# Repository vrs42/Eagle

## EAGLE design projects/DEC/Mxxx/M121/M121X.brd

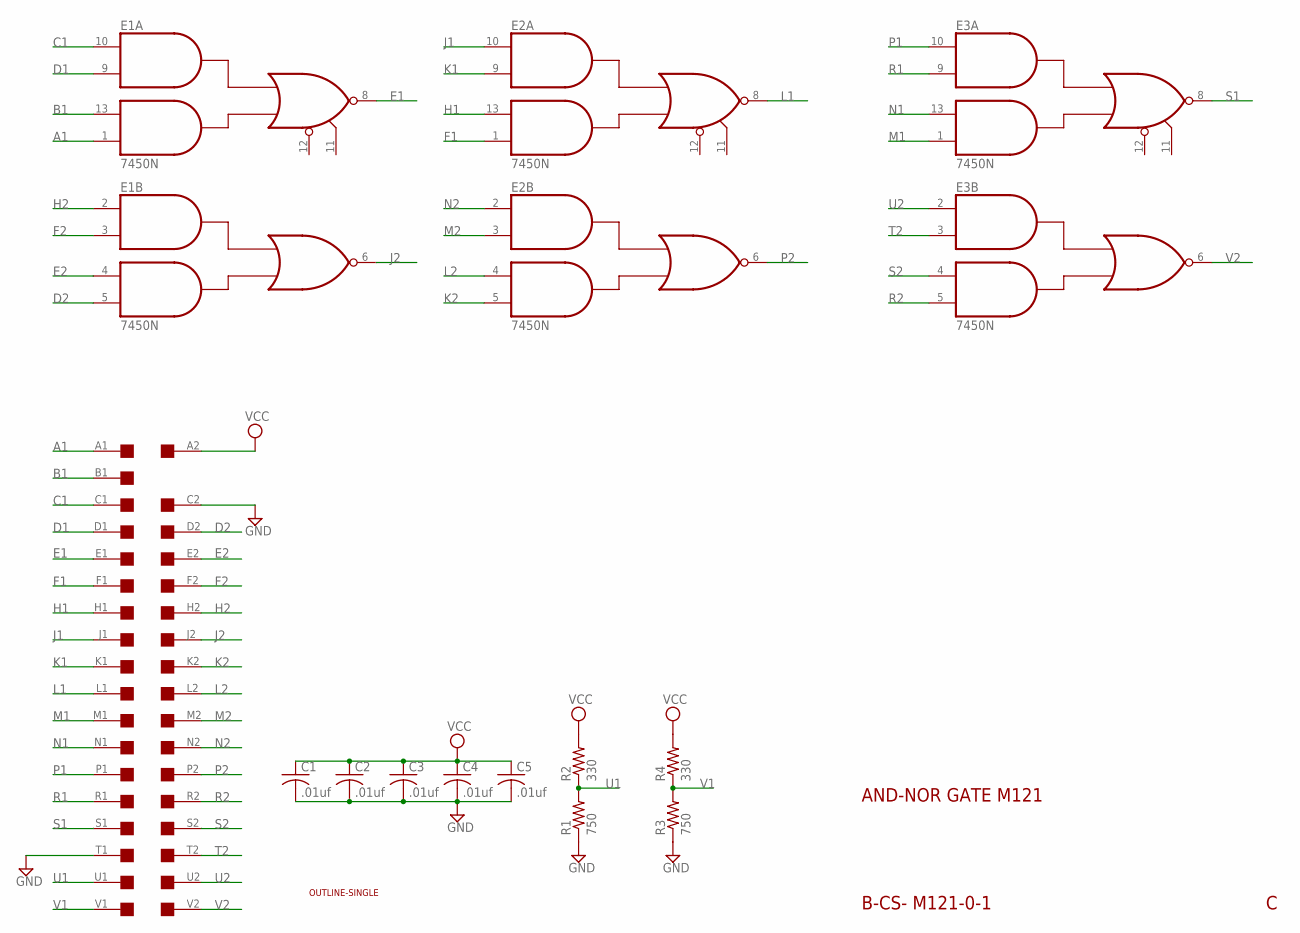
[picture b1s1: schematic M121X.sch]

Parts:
C1, C2, C3, C4, C5: .01uf; C050-025X075
E1, E2, E3: 7450N; DIL14
R1, R3: 750; 0207/10
R2, R4: 330; 0207/10
U$1: OUTLINE-SINGLE; SINGLE
U$4: SINGLE; EDGE-CON2

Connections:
A1: E1.1 (I4), U$4.A1
B1: E1.13 (I3), U$4.B1
C1: E1.10 (I1), U$4.C1
D1: E1.9 (I2), U$4.D1
D2: E1.5 (I4), U$4.D2
E1: E1.8 (O), U$4.E1
E2: E1.4 (I3), U$4.E2
F1: E2.1 (I4), U$4.F1
F2: E1.3 (I2), U$4.F2
GND: C1.2, C2.2, C3.2, C4.2, C5.2, E1.7 (GND), E2.7 (GND), E3.7 (GND), R1.1, R3.1, U$4.C2, U$4.T1
H1: E2.13 (I3), U$4.H1
H2: E1.2 (I1), U$4.H2
J1: E2.10 (I1), U$4.J1
J2: E1.6 (O), U$4.J2
K1: E2.9 (I2), U$4.K1
K2: E2.5 (I4), U$4.K2
L1: E2.8 (O), U$4.L1
L2: E2.4 (I3), U$4.L2
M1: E3.1 (I4), U$4.M1
M2: E2.3 (I2), U$4.M2
N1: E3.13 (I3), U$4.N1
N2: E2.2 (I1), U$4.N2
P1: E3.10 (I1), U$4.P1
P2: E2.6 (O), U$4.P2
R1: E3.9 (I2), U$4.R1
R2: E3.5 (I4), U$4.R2
S1: E3.8 (O), U$4.S1
S2: E3.4 (I3), U$4.S2
T2: E3.3 (I2), U$4.T2
U1: R1.2, R2.1, U$4.U1
U2: E3.2 (I1), U$4.U2
V1: R3.2, R4.1, U$4.V1
V2: E3.6 (O), U$4.V2
VCC: C1.1, C2.1, C3.1, C4.1, C5.1, E1.14 (VCC), E2.14 (VCC), E3.14 (VCC), R2.2, R4.2, U$4.A2

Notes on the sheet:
AND-NOR GATE M121
B-CS- M121-0-1

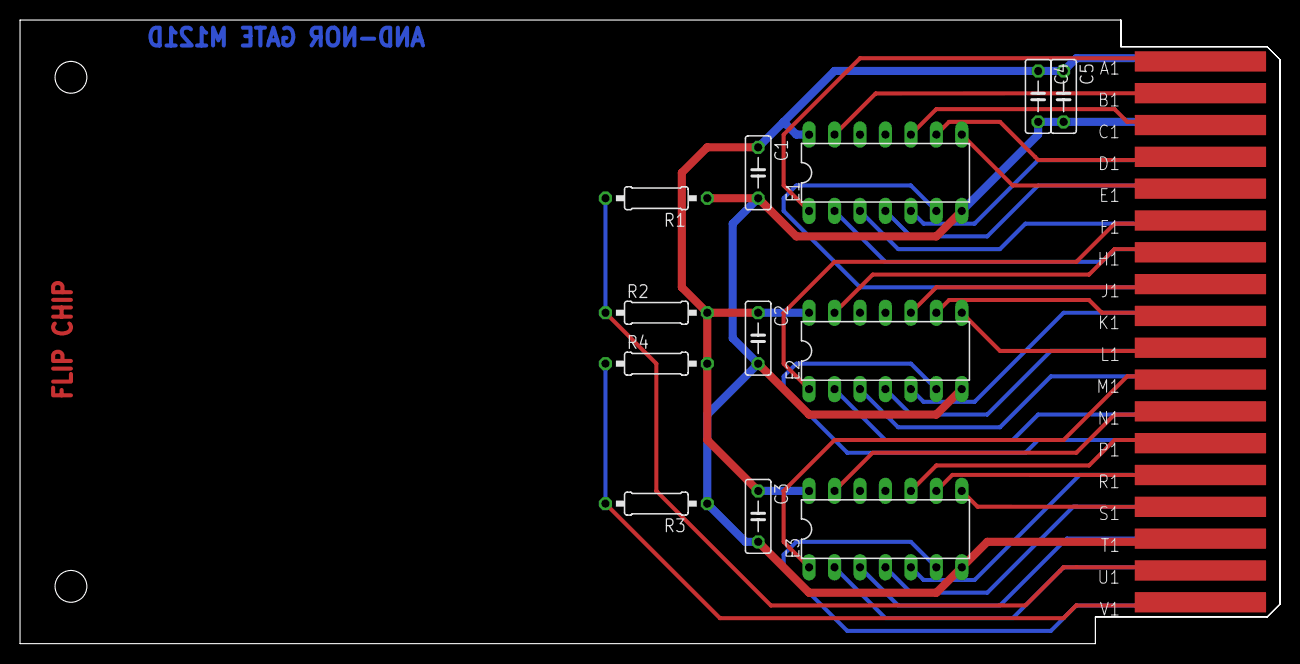
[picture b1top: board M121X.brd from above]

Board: 2 copper layers, 125.7 x 62.2 mm, 14 parts (0 on the bottom side), 34 nets.

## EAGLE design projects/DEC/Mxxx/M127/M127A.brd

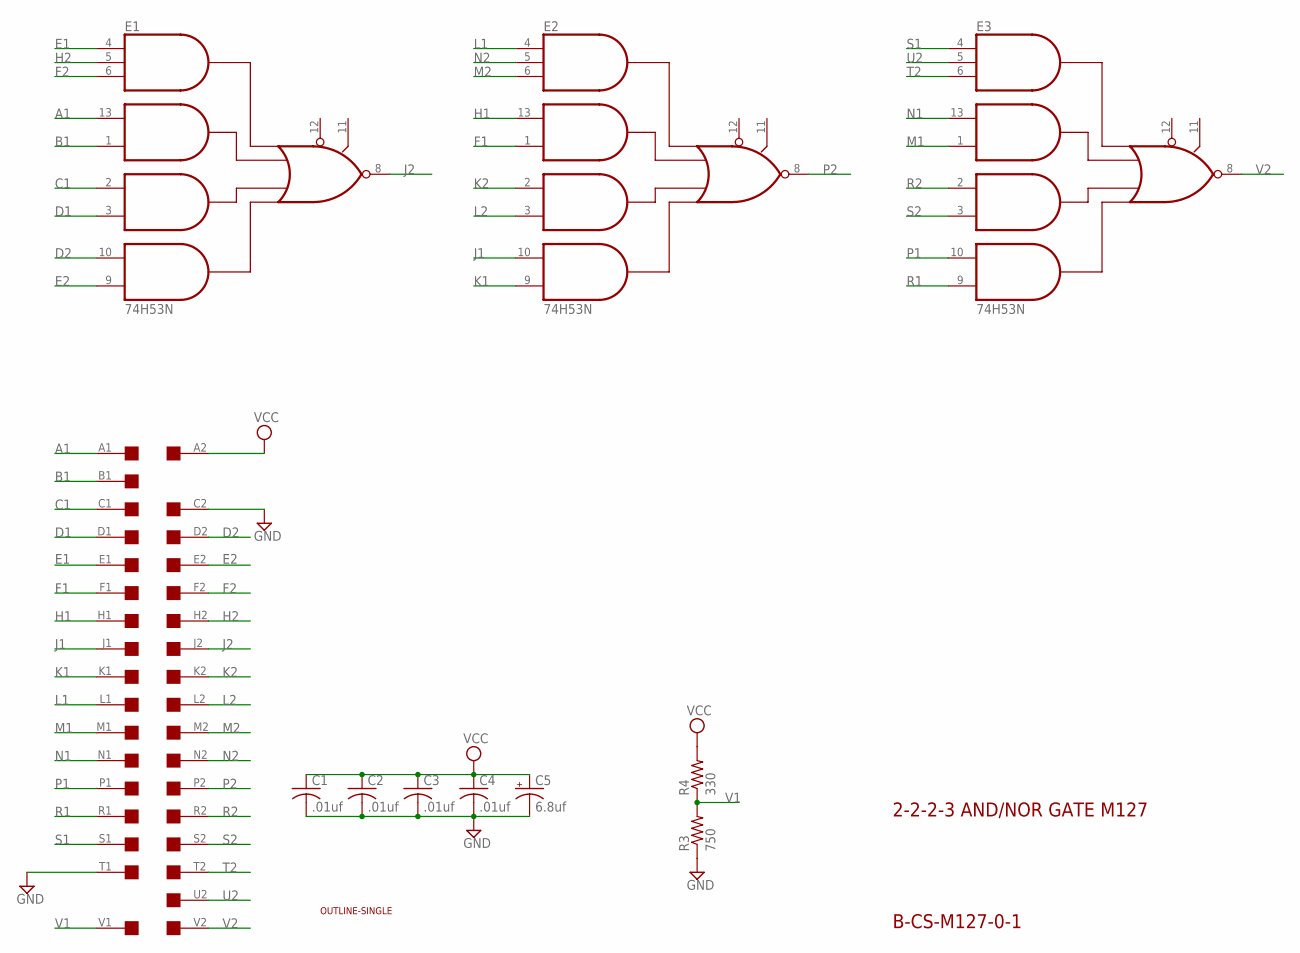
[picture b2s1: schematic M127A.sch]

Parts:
C1, C2, C3, C4: .01uf; C050-025X075
C5: 6.8uf; E15-5
E1, E2, E3: 74H53N; DIL14
R3: 750; 0207/10
R4: 330; 0207/10
U$1: OUTLINE-SINGLE; SINGLE
U$4: SINGLE; EDGE-CON2

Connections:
A1: E1.13 (I3), U$4.A1
B1: E1.1 (I4), U$4.B1
C1: E1.2 (I5), U$4.C1
D1: E1.3 (I6), U$4.D1
D2: E1.10 (I7), U$4.D2
E1: E1.4 (I1), U$4.E1
E2: E1.9 (I8), U$4.E2
F1: E2.1 (I4), U$4.F1
F2: E1.6 (I2), U$4.F2
GND: C1.2, C2.2, C3.2, C4.2, C5.-, E1.7 (GND), E2.7 (GND), E3.7 (GND), R3.1, U$4.C2, U$4.T1
H1: E2.13 (I3), U$4.H1
H2: E1.5 (I11), U$4.H2
J1: E2.10 (I7), U$4.J1
J2: E1.8 (O), U$4.J2
K1: E2.9 (I8), U$4.K1
K2: E2.2 (I5), U$4.K2
L1: E2.4 (I1), U$4.L1
L2: E2.3 (I6), U$4.L2
M1: E3.1 (I4), U$4.M1
M2: E2.6 (I2), U$4.M2
N1: E3.13 (I3), U$4.N1
N2: E2.5 (I11), U$4.N2
P1: E3.10 (I7), U$4.P1
P2: E2.8 (O), U$4.P2
R1: E3.9 (I8), U$4.R1
R2: E3.2 (I5), U$4.R2
S1: E3.4 (I1), U$4.S1
S2: E3.3 (I6), U$4.S2
T2: E3.6 (I2), U$4.T2
U2: E3.5 (I11), U$4.U2
V1: R3.2, R4.1, U$4.V1
V2: E3.8 (O), U$4.V2
VCC: C1.1, C2.1, C3.1, C4.1, C5.+, E1.14 (VCC), E2.14 (VCC), E3.14 (VCC), R4.2, U$4.A2

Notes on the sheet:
2-2-2-3 AND/NOR GATE M127
B-CS-M127-0-1

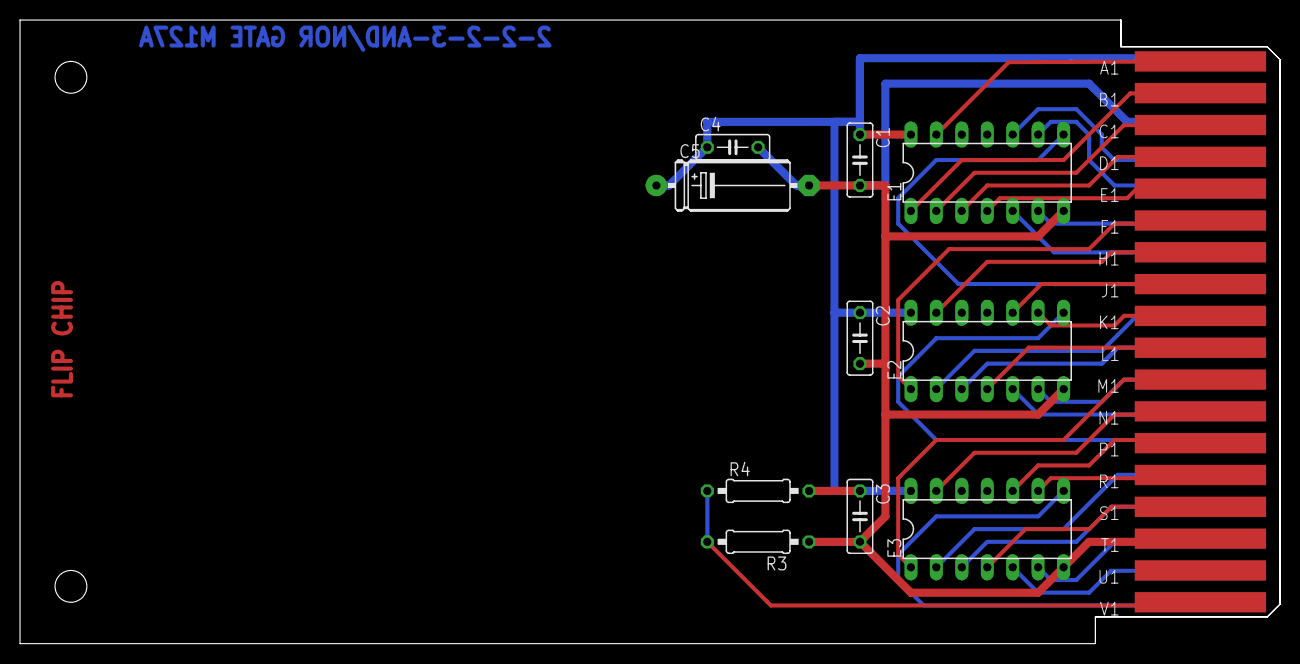
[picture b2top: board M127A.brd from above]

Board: 2 copper layers, 125.7 x 62.2 mm, 12 parts (0 on the bottom side), 33 nets.

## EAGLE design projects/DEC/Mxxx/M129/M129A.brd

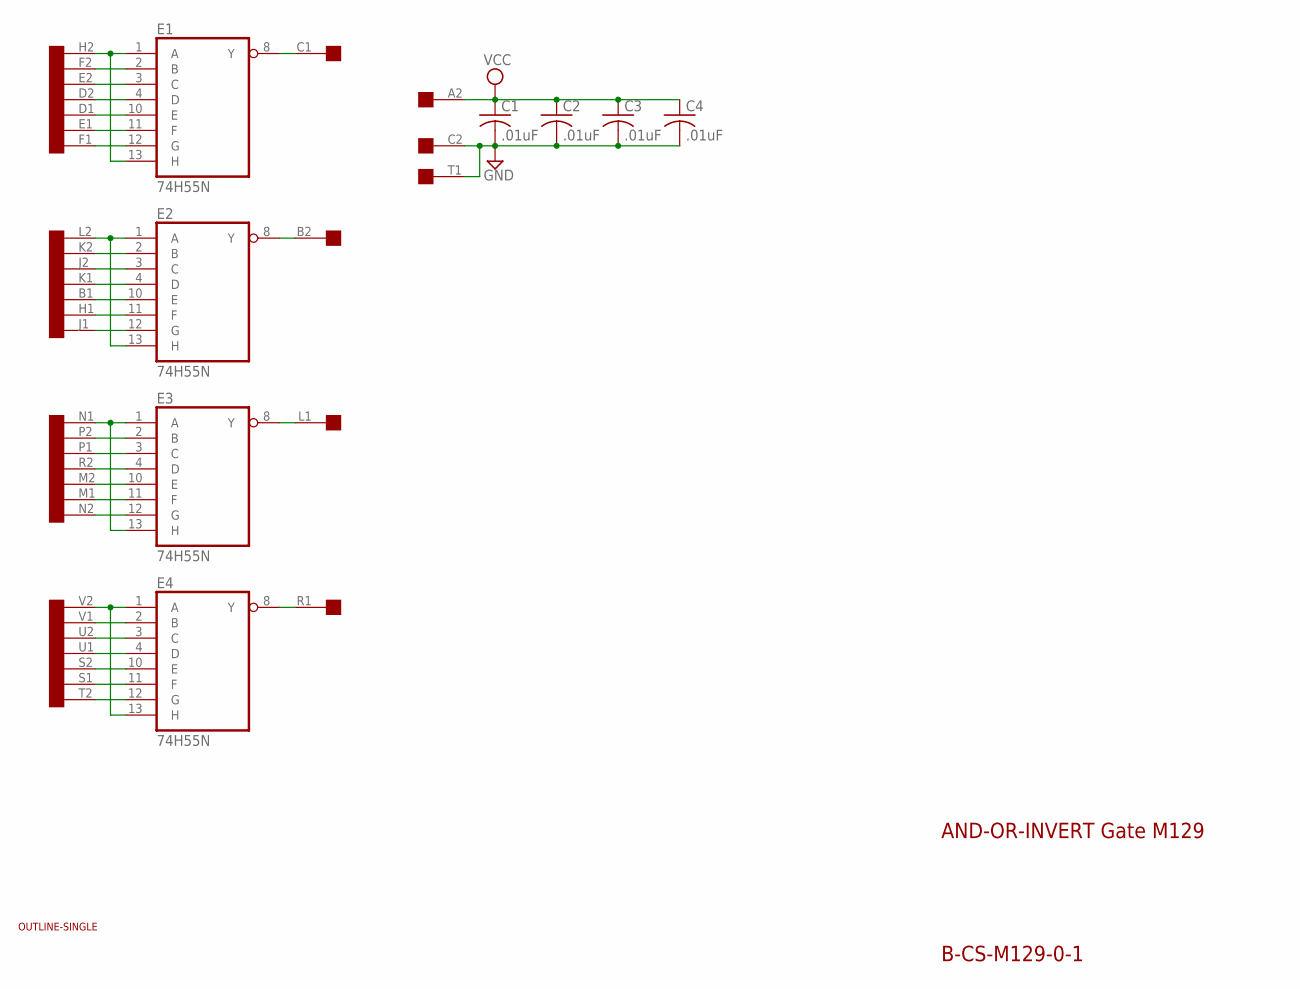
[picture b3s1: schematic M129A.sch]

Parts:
C1, C2, C3, C4: .01uF; C050-025X075
E1, E2, E3, E4: 74H55N; DIL14
U$1: SINGLE; EDGE-CON2
U$2: OUTLINE-SINGLE; SINGLE

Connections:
B1: E2.10 (E), U$1.B1
B2: E2.8 (Y), U$1.B2
C1: E1.8 (Y), U$1.C1
D1: E1.10 (E), U$1.D1
D2: E1.4 (D), U$1.D2
E1: E1.11 (F), U$1.E1
E2: E1.3 (C), U$1.E2
F1: E1.12 (G), U$1.F1
F2: E1.2 (B), U$1.F2
GND: C1.2, C2.2, C3.2, C4.2, E1.7 (GND), E2.7 (GND), E3.7 (GND), E4.7 (GND), U$1.C2, U$1.T1
H1: E2.11 (F), U$1.H1
H2: E1.1 (A), E1.13 (H), U$1.H2
J1: E2.12 (G), U$1.J1
J2: E2.3 (C), U$1.J2
K1: E2.4 (D), U$1.K1
K2: E2.2 (B), U$1.K2
L1: E3.8 (Y), U$1.L1
L2: E2.1 (A), E2.13 (H), U$1.L2
unnamed: E4.10 (E), U$1.S2
unnamed: E3.1 (A), E3.13 (H), U$1.N1
unnamed: E3.2 (B), U$1.P2
unnamed: E3.3 (C), U$1.P1
unnamed: E3.4 (D), U$1.R2
unnamed: E3.11 (F), U$1.M1
unnamed: E3.10 (E), U$1.M2
unnamed: E3.12 (G), U$1.N2
unnamed: E4.1 (A), E4.13 (H), U$1.V2
unnamed: E4.2 (B), U$1.V1
unnamed: E4.3 (C), U$1.U2
unnamed: E4.4 (D), U$1.U1
unnamed: E4.11 (F), U$1.S1
unnamed: E4.12 (G), U$1.T2
R1: E4.8 (Y), U$1.R1
VCC: C1.1, C2.1, C3.1, C4.1, E1.14 (VCC), E2.14 (VCC), E3.14 (VCC), E4.14 (VCC), U$1.A2

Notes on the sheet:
AND-OR-INVERT Gate M129
B-CS-M129-0-1

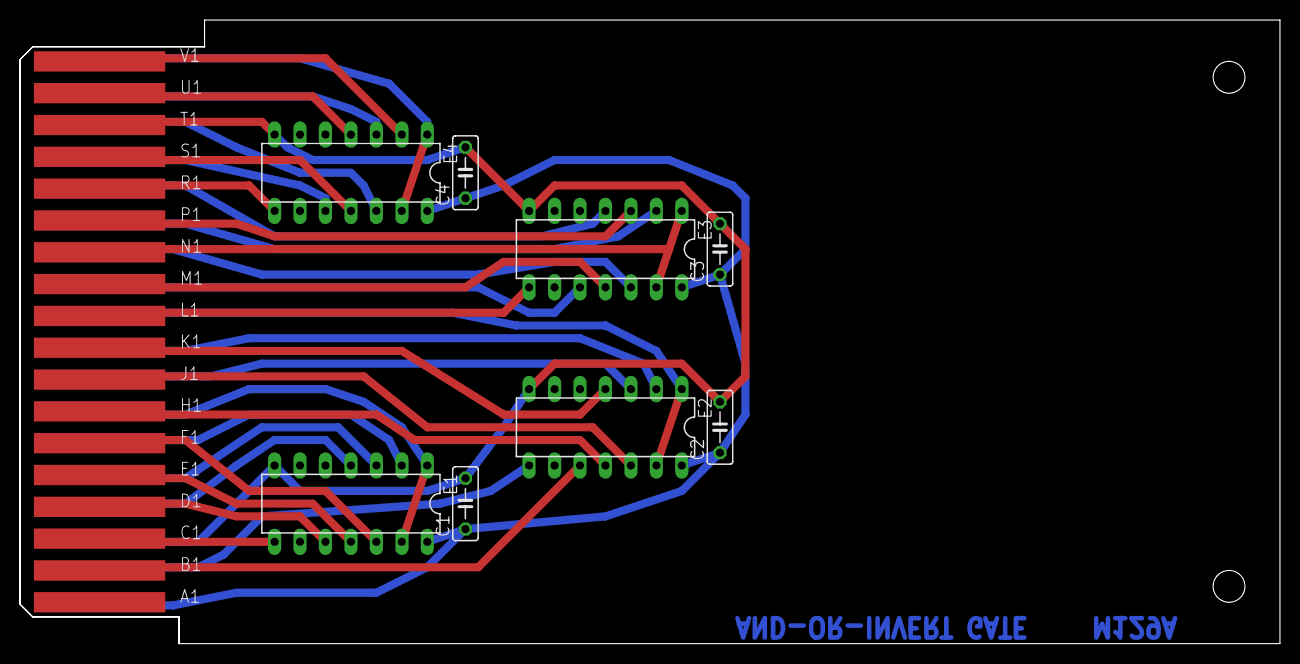
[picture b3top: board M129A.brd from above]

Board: 2 copper layers, 125.7 x 62.2 mm, 10 parts (0 on the bottom side), 34 nets.

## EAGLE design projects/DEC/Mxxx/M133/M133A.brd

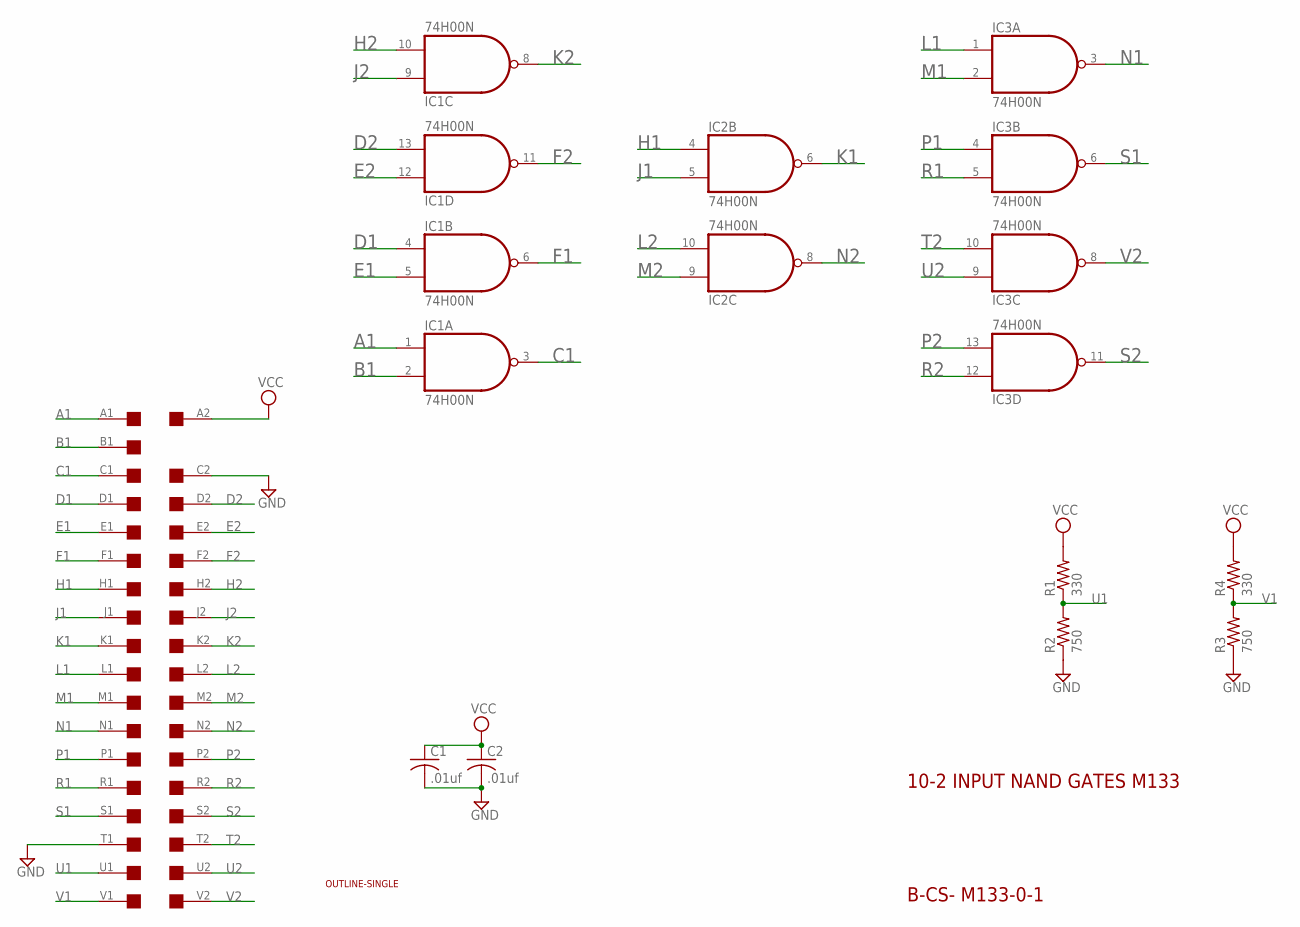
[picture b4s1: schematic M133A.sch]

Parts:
C1, C2: .01uf; C050-025X075
IC1, IC2, IC3: 74H00N; DIL14
R1, R4: 330; 0207/10
R2, R3: 750; 0207/10
U$1: OUTLINE-SINGLE; SINGLE
U$4: SINGLE; EDGE-CON2

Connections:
A1: IC1.1 (I0), U$4.A1
B1: IC1.2 (I1), U$4.B1
C1: IC1.3 (O), U$4.C1
D1: IC1.4 (I0), U$4.D1
D2: IC1.13 (I1), U$4.D2
E1: IC1.5 (I1), U$4.E1
E2: IC1.12 (I0), U$4.E2
F1: IC1.6 (O), U$4.F1
F2: IC1.11 (O), U$4.F2
GND: C1.2, C2.2, IC1.7 (GND), IC2.7 (GND), IC3.7 (GND), R2.1, R3.1, U$4.C2, U$4.T1
H1: IC2.4 (I0), U$4.H1
H2: IC1.10 (I1), U$4.H2
J1: IC2.5 (I1), U$4.J1
J2: IC1.9 (I0), U$4.J2
K1: IC2.6 (O), U$4.K1
K2: IC1.8 (O), U$4.K2
L1: IC3.1 (I0), U$4.L1
L2: IC2.10 (I1), U$4.L2
M1: IC3.2 (I1), U$4.M1
M2: IC2.9 (I0), U$4.M2
N1: IC3.3 (O), U$4.N1
N2: IC2.8 (O), U$4.N2
P1: IC3.4 (I0), U$4.P1
P2: IC3.13 (I1), U$4.P2
R1: IC3.5 (I1), U$4.R1
R2: IC3.12 (I0), U$4.R2
S1: IC3.6 (O), U$4.S1
S2: IC3.11 (O), U$4.S2
T2: IC3.10 (I1), U$4.T2
U1: R1.1, R2.2, U$4.U1
U2: IC3.9 (I0), U$4.U2
V1: R3.2, R4.1, U$4.V1
V2: IC3.8 (O), U$4.V2
VCC: C1.1, C2.1, IC1.14 (VCC), IC2.14 (VCC), IC3.14 (VCC), R1.2, R4.2, U$4.A2

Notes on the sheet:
10-2 INPUT NAND GATES M133
B-CS- M133-0-1

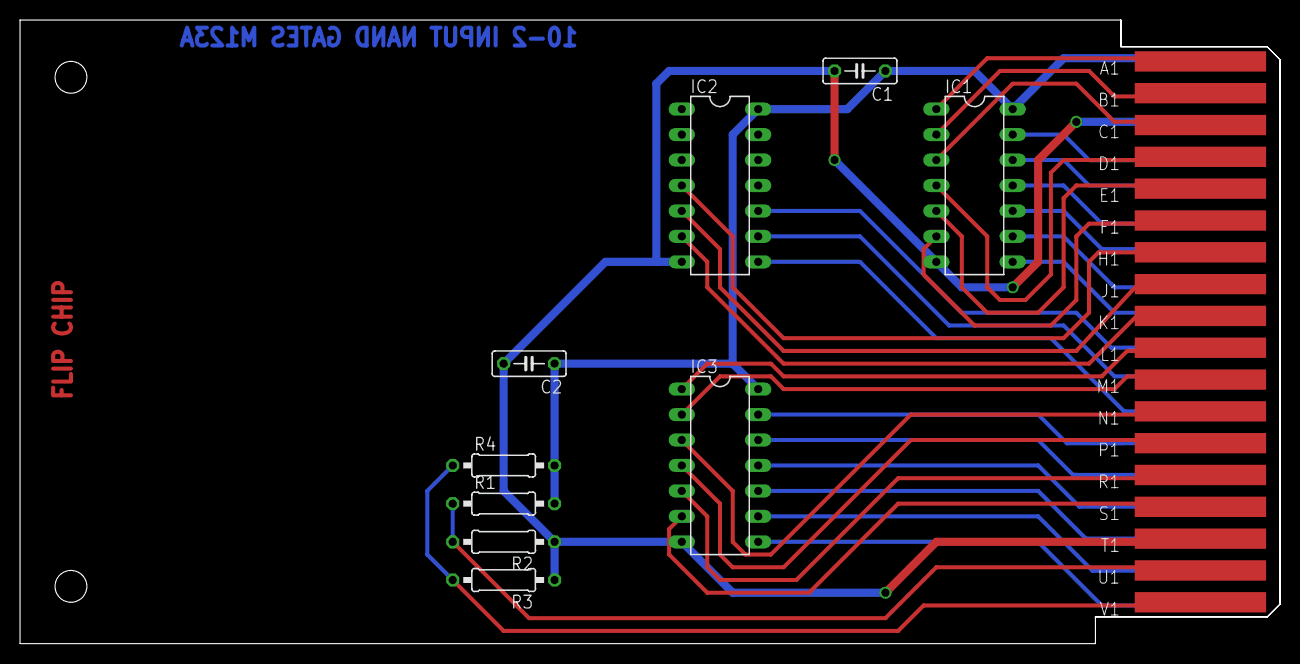
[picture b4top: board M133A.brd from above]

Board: 2 copper layers, 125.7 x 62.2 mm, 11 parts (0 on the bottom side), 34 nets.
